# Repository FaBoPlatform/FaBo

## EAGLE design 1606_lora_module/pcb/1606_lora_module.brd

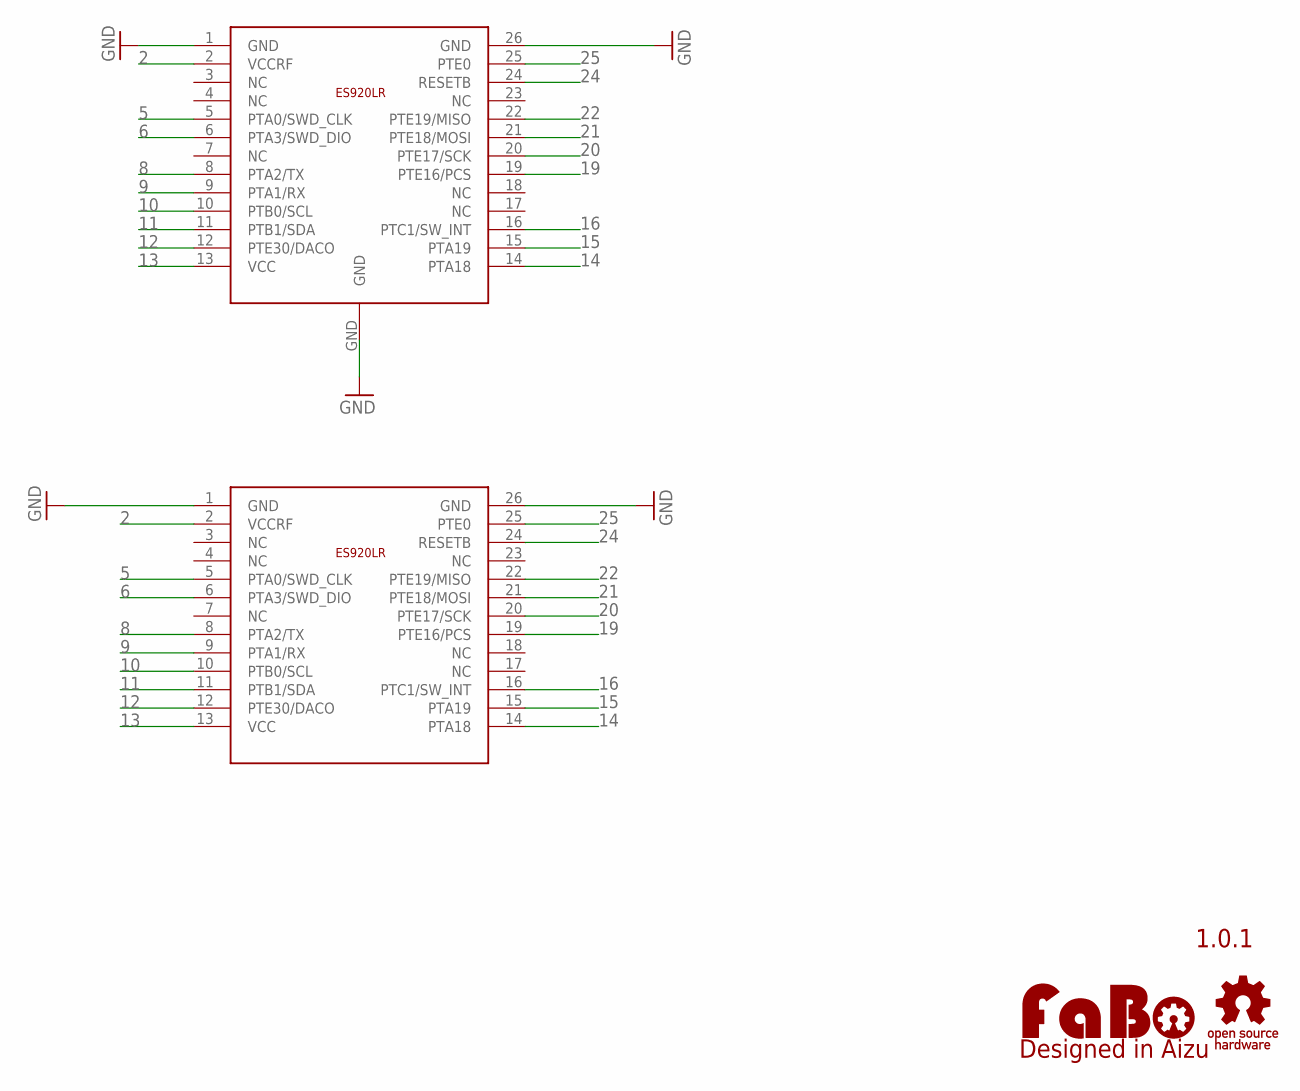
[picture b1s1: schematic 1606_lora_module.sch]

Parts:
U$2: ES920LR
U$3: ES920LR_MODULE; MODULE
U$4: LOGO_OSHW-M_BOTTOM; LOGO_OSHW_M_BOTTOM
U$5: LOGO_FABO-M_BOTTOM; LOGO_FABO_MS_BOTTOM

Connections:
2: U$2.2 (VCCRF), U$3.2 (VCCRF)
5: U$2.5 (PTA0/SWD_CLK), U$3.5 (PTA0/SWD_CLK)
6: U$2.6 (PTA3/SWD_DIO), U$3.6 (PTA3/SWD_DIO)
8: U$2.8 (PTA2/TX), U$3.8 (PTA2/TX)
9: U$2.9 (PTA1/RX), U$3.9 (PTA1/RX)
10: U$2.10 (PTB0/SCL), U$3.10 (PTB0/SCL)
11: U$2.11 (PTB1/SDA), U$3.11 (PTB1/SDA)
12: U$2.12 (PTE30/DACO), U$3.12 (PTE30/DACO)
13: U$2.13 (VCC), U$3.13 (VCC)
14: U$2.14 (PTA18), U$3.14 (PTA18)
15: U$2.15 (PTA19), U$3.15 (PTA19)
16: U$2.16 (PTC1/SW_INT), U$3.16 (PTC1/SW_INT)
19: U$2.19 (PTE16/PCS), U$3.19 (PTE16/PCS)
20: U$2.20 (PTE17/SCK), U$3.20 (PTE17/SCK)
21: U$2.21 (PTE18/MOSI), U$3.21 (PTE18/MOSI)
22: U$2.22 (PTE19/MISO), U$3.22 (PTE19/MISO)
24: U$2.24 (RESETB), U$3.24 (RESETB)
25: U$2.25 (PTE0), U$3.25 (PTE0)
GND: U$2.1 (GND), U$2.26 (GND), U$2.GND, U$3.1 (GND), U$3.26 (GND)

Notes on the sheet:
1.0.1

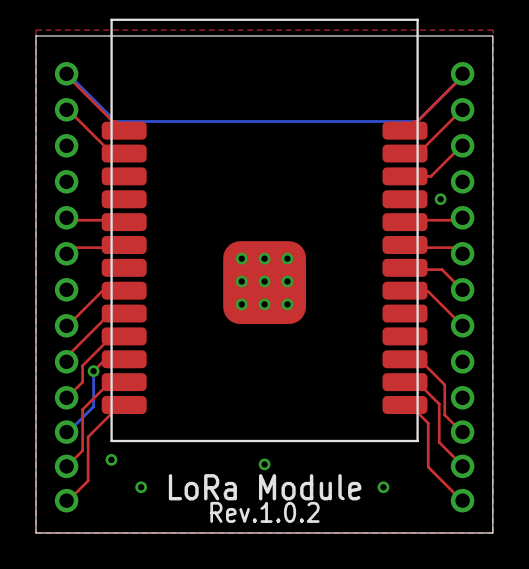
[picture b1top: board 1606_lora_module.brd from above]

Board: 2 copper layers, 25.4 x 27.6 mm, 4 parts (0 on the bottom side), 19 nets.

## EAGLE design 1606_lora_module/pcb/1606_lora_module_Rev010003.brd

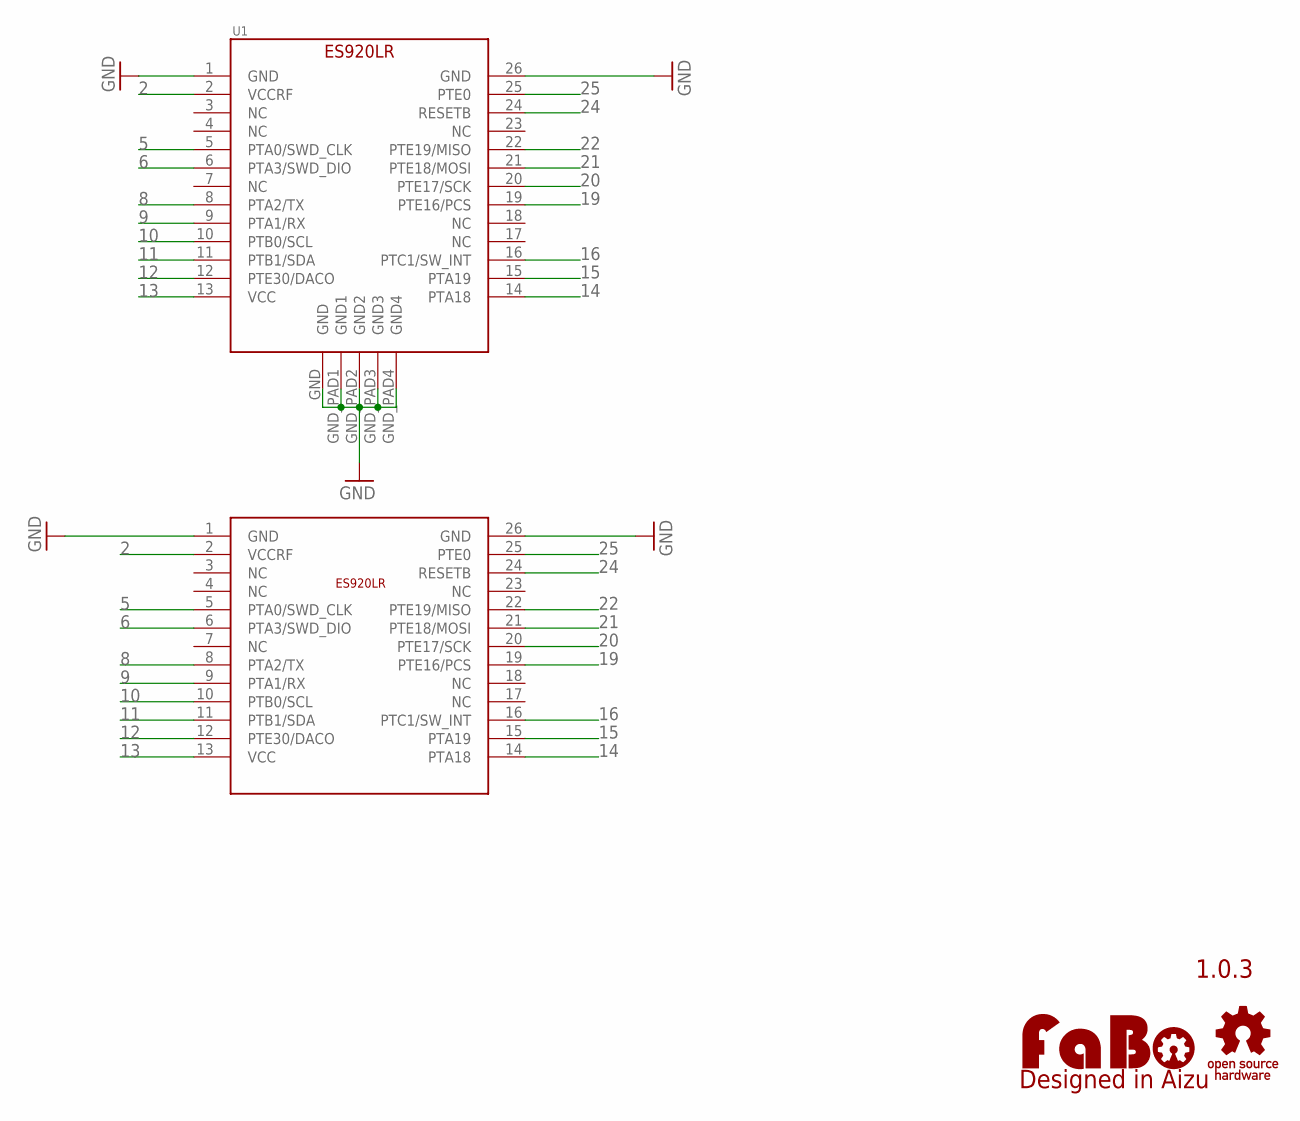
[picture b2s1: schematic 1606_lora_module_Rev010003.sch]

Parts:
U1: ES920LR
U$3: ES920LR_MODULE; MODULE
U$4: LOGO_OSHW-M_BOTTOM; LOGO_OSHW_M_BOTTOM
U$5: LOGO_FABO-M_BOTTOM; LOGO_FABO_MS_BOTTOM

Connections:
2: U1.2 (VCCRF), U$3.2 (VCCRF)
5: U1.5 (PTA0/SWD_CLK), U$3.5 (PTA0/SWD_CLK)
6: U1.6 (PTA3/SWD_DIO), U$3.6 (PTA3/SWD_DIO)
8: U1.8 (PTA2/TX), U$3.8 (PTA2/TX)
9: U1.9 (PTA1/RX), U$3.9 (PTA1/RX)
10: U1.10 (PTB0/SCL), U$3.10 (PTB0/SCL)
11: U1.11 (PTB1/SDA), U$3.11 (PTB1/SDA)
12: U1.12 (PTE30/DACO), U$3.12 (PTE30/DACO)
13: U1.13 (VCC), U$3.13 (VCC)
14: U1.14 (PTA18), U$3.14 (PTA18)
15: U1.15 (PTA19), U$3.15 (PTA19)
16: U1.16 (PTC1/SW_INT), U$3.16 (PTC1/SW_INT)
19: U1.19 (PTE16/PCS), U$3.19 (PTE16/PCS)
20: U1.20 (PTE17/SCK), U$3.20 (PTE17/SCK)
21: U1.21 (PTE18/MOSI), U$3.21 (PTE18/MOSI)
22: U1.22 (PTE19/MISO), U$3.22 (PTE19/MISO)
24: U1.24 (RESETB), U$3.24 (RESETB)
25: U1.25 (PTE0), U$3.25 (PTE0)
GND: U1.1 (GND), U1.26 (GND), U1.GND, U1.GND_PAD1 (GND1), U1.GND_PAD2 (GND2), U1.GND_PAD3 (GND3), U1.GND_PAD4 (GND4), U$3.1 (GND), U$3.26 (GND)

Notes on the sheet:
1.0.3

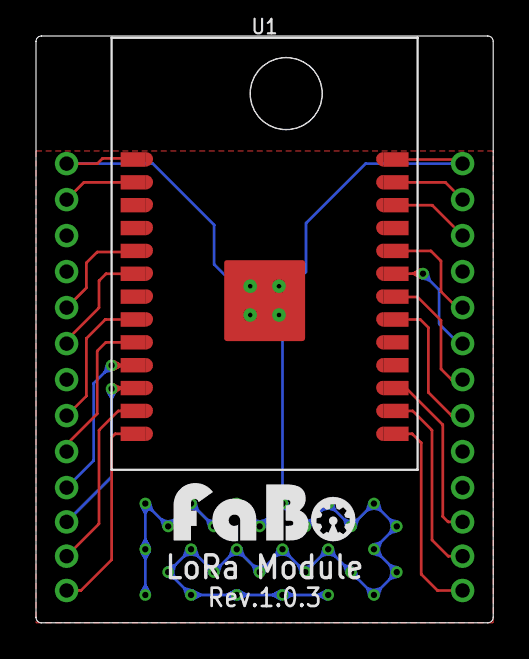
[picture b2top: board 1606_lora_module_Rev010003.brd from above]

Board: 2 copper layers, 25.4 x 32.6 mm, 4 parts (1 on the bottom side), 19 nets.

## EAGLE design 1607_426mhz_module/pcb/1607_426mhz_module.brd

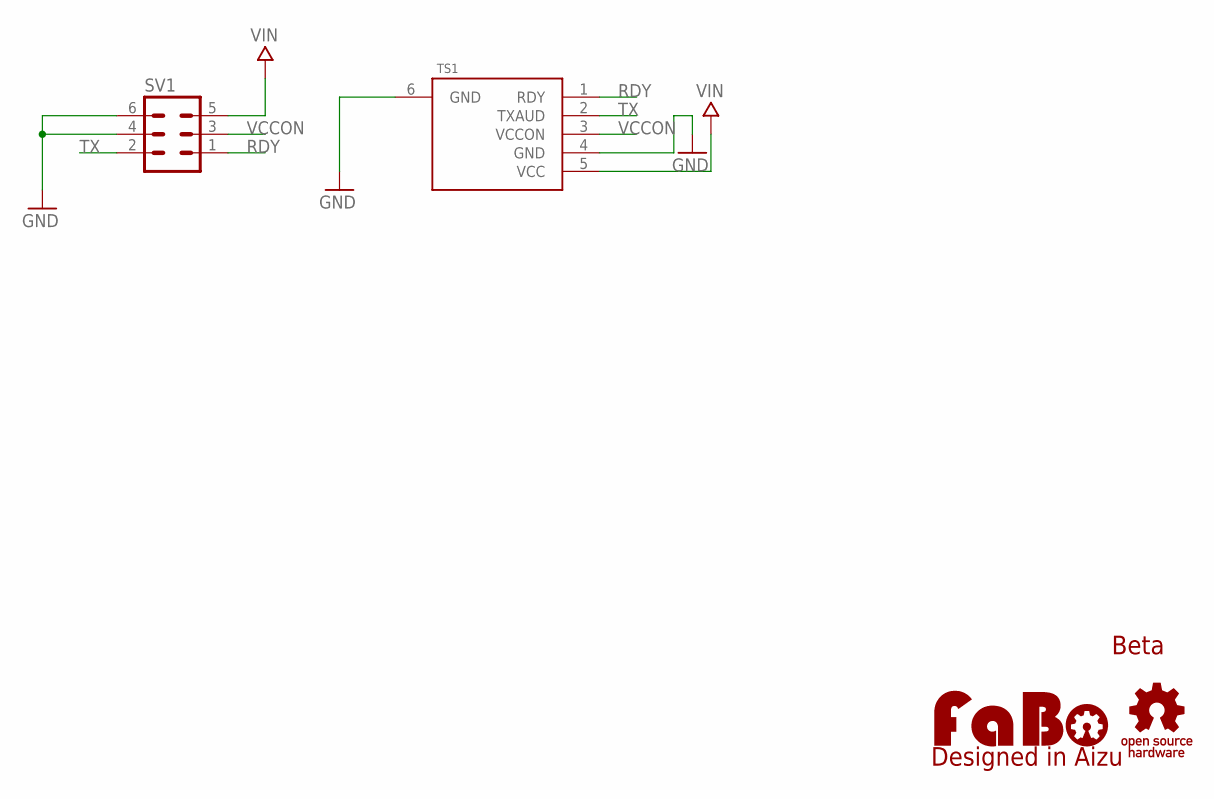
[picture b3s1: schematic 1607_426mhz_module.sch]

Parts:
SV1: MA03-2
TS1: TS01E
U$3: LOGO_OSHW-M_BOTTOM; LOGO_OSHW_M_BOTTOM
U$4: LOGO_FABO-M_BOTTOM; LOGO_FABO_MS_BOTTOM

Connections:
GND: SV1.4, SV1.6, TS1.4 (GND), TS1.6 (GND)
RDY: SV1.1, TS1.1 (RDY)
TX: SV1.2, TS1.2 (TXAUD)
VCCON: SV1.3, TS1.3 (VCCON)
VIN: SV1.5, TS1.5 (VCC)

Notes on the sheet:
Beta

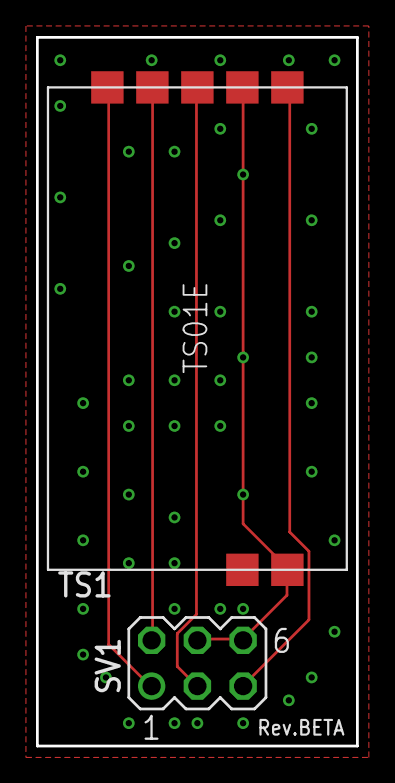
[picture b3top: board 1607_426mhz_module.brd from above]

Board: 2 copper layers, 17.8 x 39.4 mm, 4 parts (0 on the bottom side), 5 nets.

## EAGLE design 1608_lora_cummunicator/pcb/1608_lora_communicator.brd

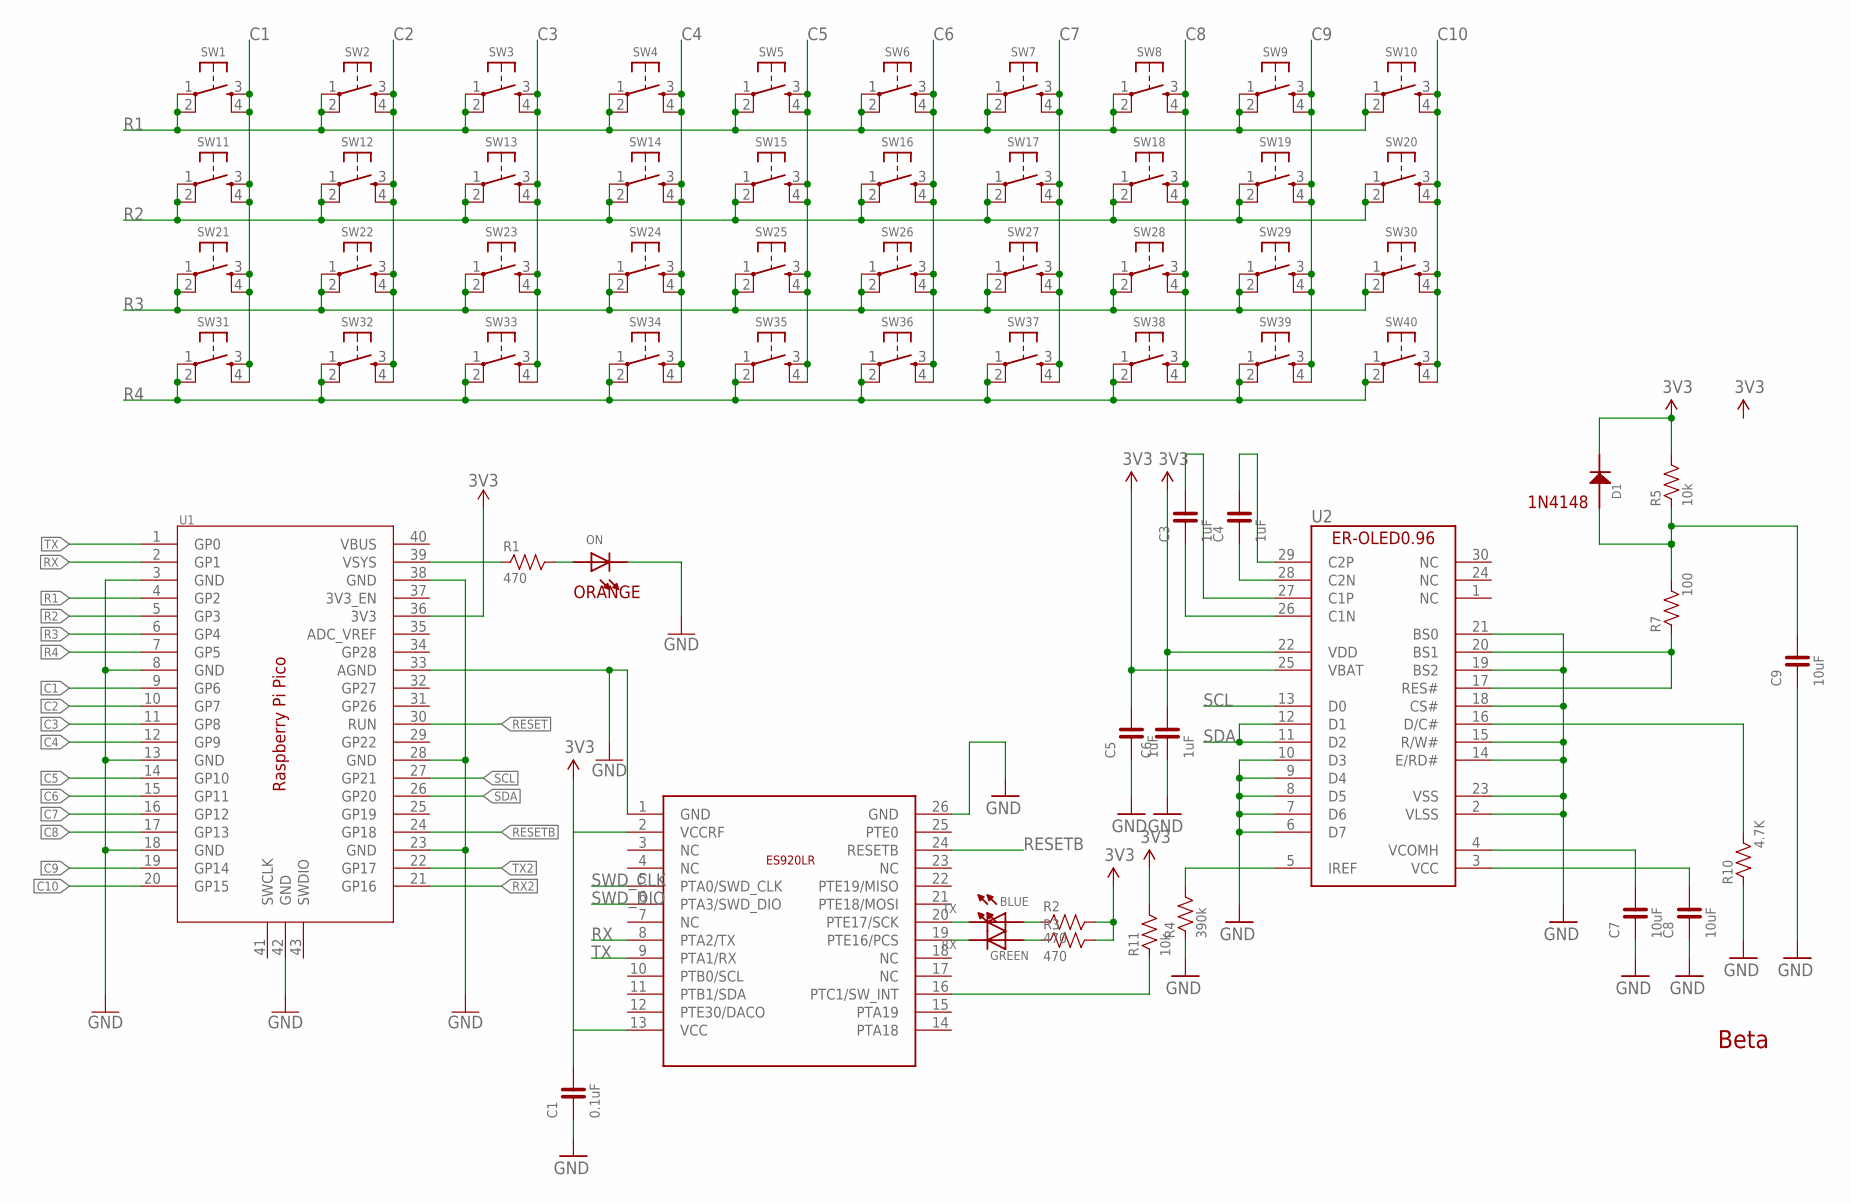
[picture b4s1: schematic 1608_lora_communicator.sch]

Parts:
C1: 0.1uF; 0603-NARROW
C3, C4, C5, C6: 1uF; 0603
C7, C8, C9: 10uF; 0603
D1: 1N4148; 1N4148W
ON: LED-0603; 0603
R1, R2, R3: 470; 0603
R4: 390k; 0603
R5: 10k; 0603
R7: 100; 0603
R10: 4.7K; 0603
R11: 10k; 0603-NARROW
RX: GREEN; 0603
SW1, SW2, SW3, SW4, SW5, SW6, SW7, SW8, SW9, SW10, SW11, SW12, SW13, SW14, SW15, SW16, SW17, SW18, SW19, SW20, SW21, SW22, SW23, SW24, SW25, SW26, SW27, SW28, SW29, SW30, SW31, SW32, SW33, SW34, SW35, SW36, SW37, SW38, SW39, SW40: TACT-SWITCH-6MM; DTS_6_V
TX: BLUE; 0603
U1: RASPBERRY_PI_PICORASPBERRY_PI_PICO_2BY20TH; RASPBERRY_PI_PICO_HEADER_BOTH
U2: ER-OLED0.96-1ER-CON30HT-1; ER-CON30HT-1
U3: ES920LR_MODULE; MODULE

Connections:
3V3: C1.2, C5.2, C6.2, D1.CATHODE, R2.2, R3.2, R5.2, R11.2, U1.36 (3V3), U2.22 (VDD), U2.25 (VBAT), U3.2 (VCCRF), U3.13 (VCC)
C1: SW1.3, SW1.4, SW11.3, SW11.4, SW21.3, SW21.4, SW31.3, SW31.4, U1.9 (GP6)
C2: SW2.3, SW2.4, SW12.3, SW12.4, SW22.3, SW22.4, SW32.3, SW32.4, U1.10 (GP7)
C3: SW3.3, SW3.4, SW13.3, SW13.4, SW23.3, SW23.4, SW33.3, SW33.4, U1.11 (GP8)
C4: SW4.3, SW4.4, SW14.3, SW14.4, SW24.3, SW24.4, SW34.3, SW34.4, U1.12 (GP9)
C5: SW5.3, SW5.4, SW15.3, SW15.4, SW25.3, SW25.4, SW35.3, SW35.4, U1.14 (GP10)
C6: SW6.3, SW6.4, SW16.3, SW16.4, SW26.3, SW26.4, SW36.3, SW36.4, U1.15 (GP11)
C7: SW7.3, SW7.4, SW17.3, SW17.4, SW27.3, SW27.4, SW37.3, SW37.4, U1.16 (GP12)
C8: SW8.3, SW8.4, SW18.3, SW18.4, SW28.3, SW28.4, SW38.3, SW38.4, U1.17 (GP13)
C9: SW9.3, SW9.4, SW19.3, SW19.4, SW29.3, SW29.4, SW39.3, SW39.4, U1.19 (GP14)
C10: SW10.3, SW10.4, SW20.3, SW20.4, SW30.3, SW30.4, SW40.3, SW40.4, U1.20 (GP15)
D/C: R10.2, U2.16 (D/C#)
GND: C1.1, C5.1, C6.1, C7.1, C8.1, C9.1, ON.CATHODE, R4.1, R10.1, U1.3 (GND), U1.8 (GND), U1.13 (GND), U1.18 (GND), U1.23 (GND), U1.28 (GND), U1.33 (AGND), U1.38 (GND), U1.42 (GND), U2.2 (VLSS), U2.6 (D7), U2.7 (D6), U2.8 (D5), U2.9 (D4), U2.10 (D3), U2.14 (E/RD#), U2.15 (R/W#), U2.18 (CS#), U2.19 (BS2), U2.21 (BS0), U2.23 (VSS), U3.1 (GND)
unnamed: R1.1, U1.39 (VSYS)
unnamed: ON.ANODE, R1.2, U3.26 (GND)
unnamed: C3.2, U2.27 (C1P)
unnamed: C3.1, U2.26 (C1N)
unnamed: C4.1, U2.28 (C2N)
unnamed: C4.2, U2.29 (C2P)
unnamed: R4.2, U2.5 (IREF)
unnamed: C7.2, U2.4 (VCOMH)
unnamed: C8.2, U2.3 (VCC)
unnamed: R7.1, U2.17 (RES#), U2.20 (BS1)
unnamed: RX.CATHODE, U3.19 (PTE16/PCS)
unnamed: C9.2, D1.ANODE, R5.1, R7.2
unnamed: TX.CATHODE, U3.20 (PTE17/SCK)
unnamed: R2.1, TX.ANODE
unnamed: R3.1, RX.ANODE
unnamed: R11.1, U3.16 (PTC1/SW_INT)
R1: SW1.1, SW1.2, SW2.1, SW2.2, SW3.1, SW3.2, SW4.1, SW4.2, SW5.1, SW5.2, SW6.1, SW6.2, SW7.1, SW7.2, SW8.1, SW8.2, SW9.1, SW9.2, SW10.1, SW10.2, U1.4 (GP2)
R2: SW11.1, SW11.2, SW12.1, SW12.2, SW13.1, SW13.2, SW14.1, SW14.2, SW15.1, SW15.2, SW16.1, SW16.2, SW17.1, SW17.2, SW18.1, SW18.2, SW19.1, SW19.2, SW20.1, SW20.2, U1.5 (GP3)
R3: SW21.1, SW21.2, SW22.1, SW22.2, SW23.1, SW23.2, SW24.1, SW24.2, SW25.1, SW25.2, SW26.1, SW26.2, SW27.1, SW27.2, SW28.1, SW28.2, SW29.1, SW29.2, SW30.1, SW30.2, U1.6 (GP4)
R4: SW31.1, SW31.2, SW32.1, SW32.2, SW33.1, SW33.2, SW34.1, SW34.2, SW35.1, SW35.2, SW36.1, SW36.2, SW37.1, SW37.2, SW38.1, SW38.2, SW39.1, SW39.2, SW40.1, SW40.2, U1.7 (GP5)
RESET: U1.30 (RUN)
RESETB: U1.24 (GP18), U3.24 (RESETB)
RX: U1.2 (GP1), U3.8 (PTA2/TX)
RX2: U1.21 (GP16)
SCL: U1.27 (GP21), U2.13 (D0)
SDA: U1.26 (GP20), U2.11 (D2), U2.12 (D1)
SWD_CLK: U3.5 (PTA0/SWD_CLK)
SWD_DIO: U3.6 (PTA3/SWD_DIO)
TX: U1.1 (GP0), U3.9 (PTA1/RX)
TX2: U1.22 (GP17)

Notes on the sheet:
Beta
ORANGE
1N4148

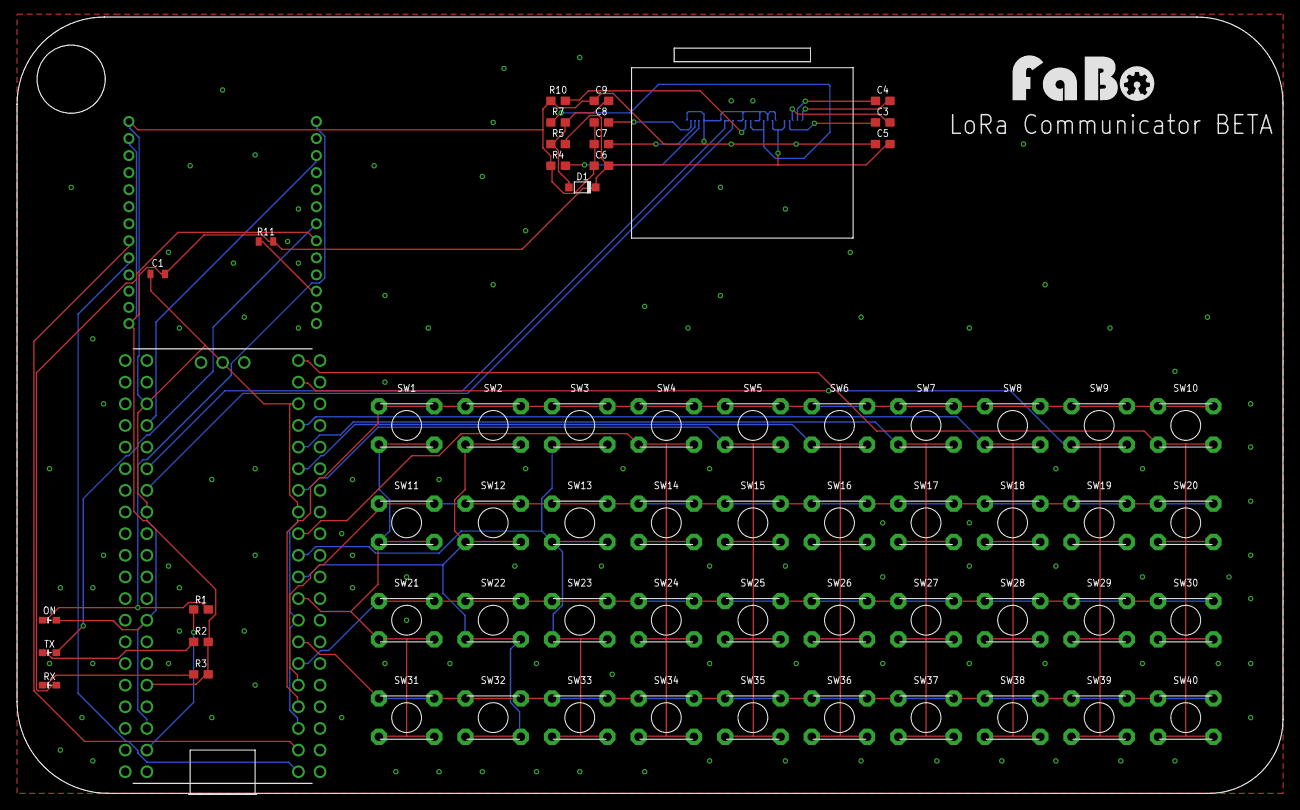
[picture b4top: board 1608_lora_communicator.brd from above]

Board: 2 copper layers, 148.6 x 91.1 mm, 64 parts (0 on the bottom side), 38 nets.

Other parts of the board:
U$2: LOGO_FABO_L

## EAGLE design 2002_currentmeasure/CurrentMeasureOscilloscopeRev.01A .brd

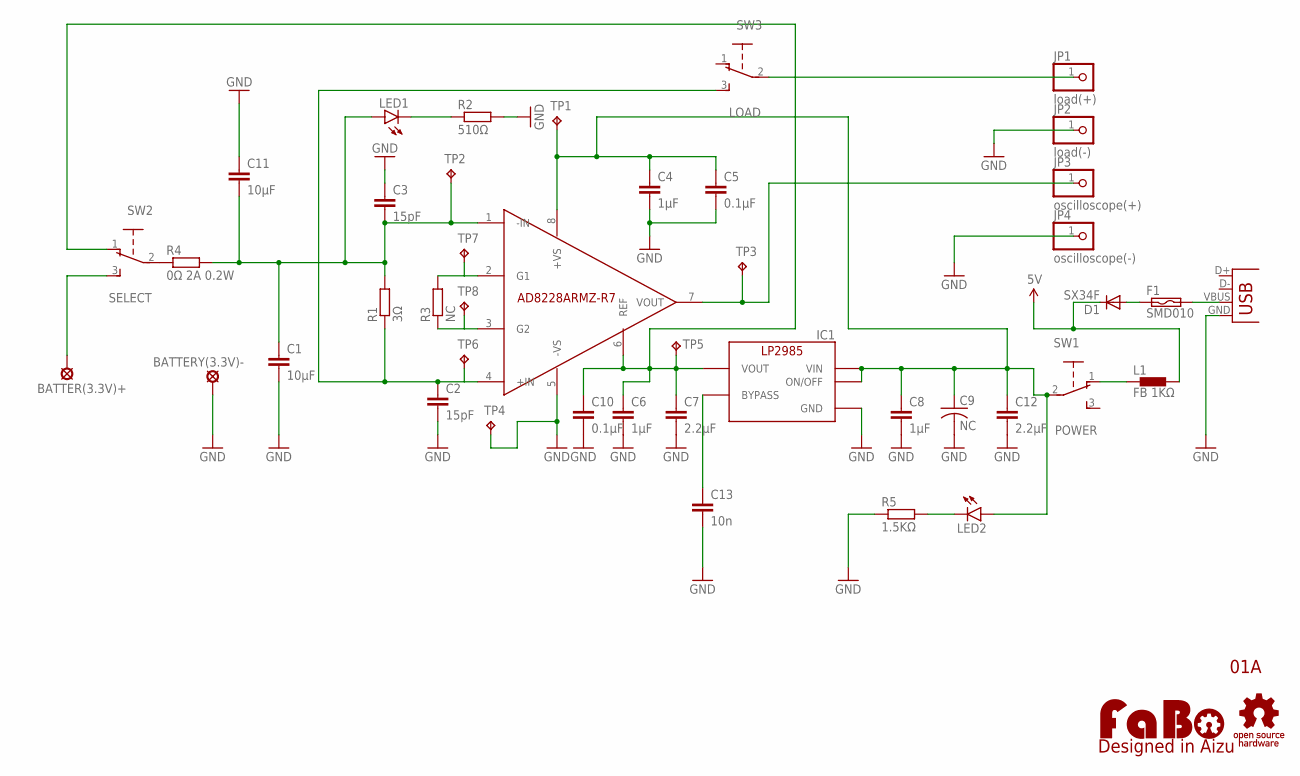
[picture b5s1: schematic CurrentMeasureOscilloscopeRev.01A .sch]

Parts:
BATTER(3.3V)+: SE14
BATTERY(3.3V)-: SE14
C1, C11: 10μF; C0805
C2, C3: 15pF; C0402
C4: 1μF; C0603
C5, C10: 0.1μF; C0402
C6, C8: 1μF; C0805
C7, C12: 2.2μF; C1206K
C9: NC; C2012
C13: 10n; C2012
D1: SX34F; SOD106-R
F1: SMD010
IC1: TI-LP2985-33DBVR; TI-LP2985
JP1: load(+); 1X01
JP2: load(-); 1X01
JP3: oscilloscope(+); 1X01
JP4: oscilloscope(-); 1X01
JP5: USB-B-MICRO_SMD; USB_B_MICRO
L1: FB 1KΩ; 0402
LED1, LED2: LED-EIA0603; EIA0603-LED
R1: 3Ω; M1206
R2: 510Ω; R0402
R3: NC; M1206
R4: 0Ω 2A 0.2W; R0402
R5: 1.5KΩ; R0603
SW1: POWER; EG1218
SW2: SELECT; EG1218
SW3: LOAD; EG1218
TP1, TP2, TP3, TP4, TP5, TP6, TP7, TP8: TPTP13R; TP13R
U1: AD8228ADZY; MSOP08
U$2: LOGO_OSHW-M_BOTTOM; LOGO_OSHW_M_BOTTOM
U$3: LOGO_FABO-M; LOGO_FABO_MS

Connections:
5V: D1.C, L1.2
GND: BATTERY(3.3V)-.MP, C1.2, C2.2, C3.1, C4.2, C5.2, C6.2, C7.2, C8.2, C9.2, C10.2, C11.1, C12.2, C13.2, IC1.2 (GND), JP2.1, JP4.1, JP5.GND, R2.2, R5.1, TP4.TP, U1.5 (-VS)
unnamed: C1.1, C3.2, C11.2, LED1.A, R1.2, R4.2, TP2.TP, U1.1 (-IN)
unnamed: C4.1, C5.1, C8.1, C9.1, C12.1, IC1.1 (VIN), IC1.3 (ON/OFF), LED2.A, SW1.2, TP1.TP, U1.8 (+VS)
unnamed: C2.1, R1.1, SW3.3, TP6.TP, U1.4 (+IN)
unnamed: LED1.C, R2.1
unnamed: JP3.1, TP3.TP, U1.7 (VOUT)
unnamed: R3.2, TP7.TP, U1.2 (G1)
unnamed: R3.1, TP8.TP, U1.3 (G2)
unnamed: BATTER(3.3V)+.MP, SW2.3
unnamed: JP1.1, SW3.2
unnamed: R4.1, SW2.2
unnamed: C6.1, C7.1, C10.1, IC1.5 (VOUT), SW2.1, TP5.TP, U1.6 (REF)
unnamed: C13.1, IC1.4 (BYPASS)
unnamed: LED2.C, R5.2
unnamed: L1.1, SW1.1
unnamed: D1.A, F1.P$1 (1)
unnamed: F1.P$2 (2), JP5.VBUS

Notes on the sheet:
AD8228ARMZ-R7
01A

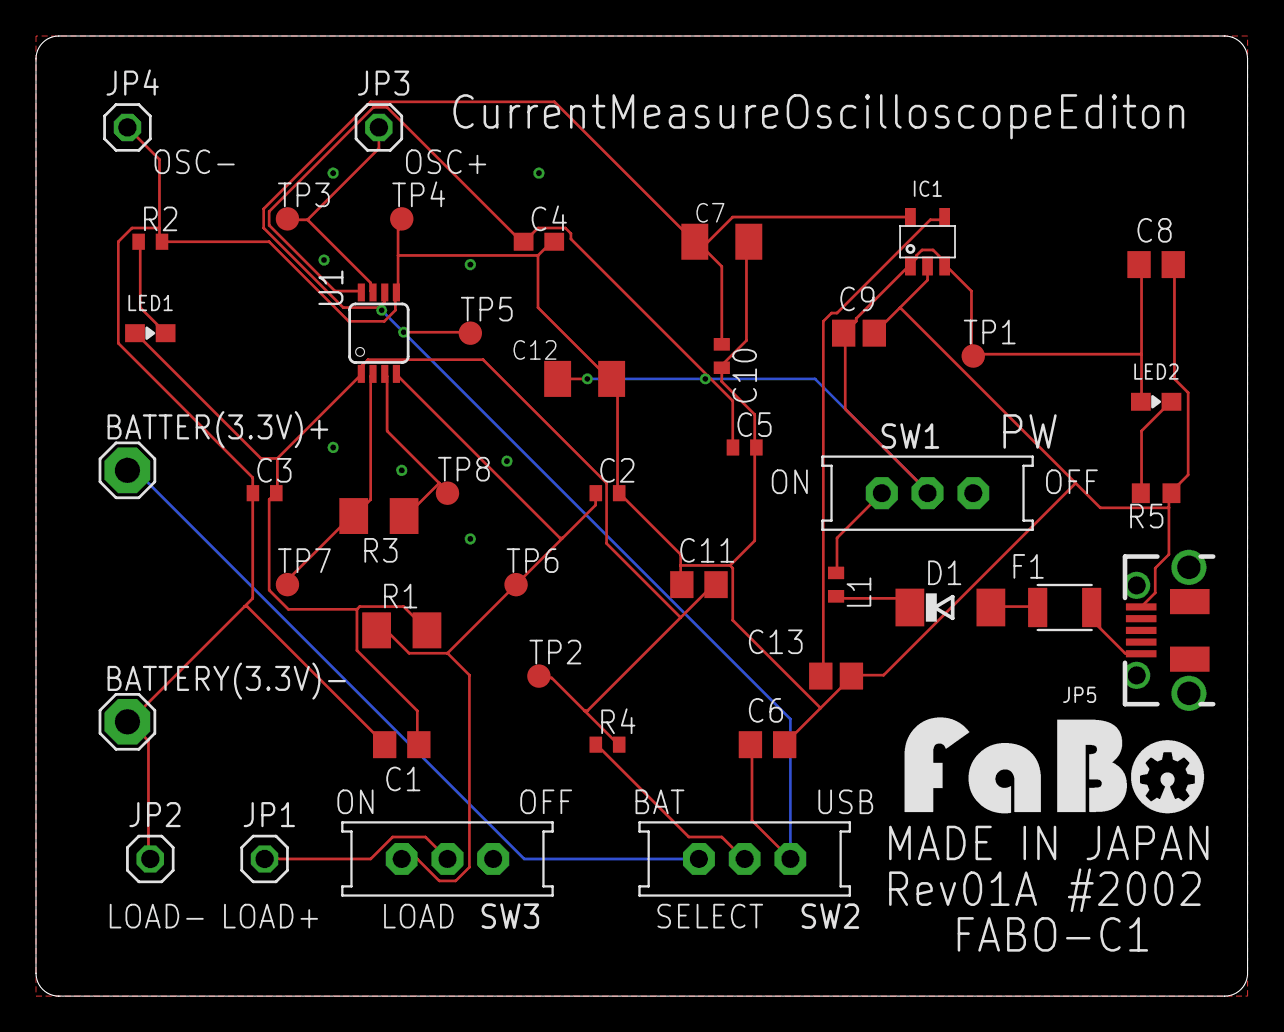
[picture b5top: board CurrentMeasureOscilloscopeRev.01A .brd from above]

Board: 2 copper layers, 67.3 x 53.3 mm, 44 parts (0 on the bottom side), 18 nets.

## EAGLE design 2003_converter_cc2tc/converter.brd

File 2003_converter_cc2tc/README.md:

# #2003 Converter

## Overview

CC DebuggerからTagConnecterへの変換をおこないます。

## 回路図

## Github

https://github.com/FaBoPlatform/FaBo/tree/master/2003_converter_cc2tc

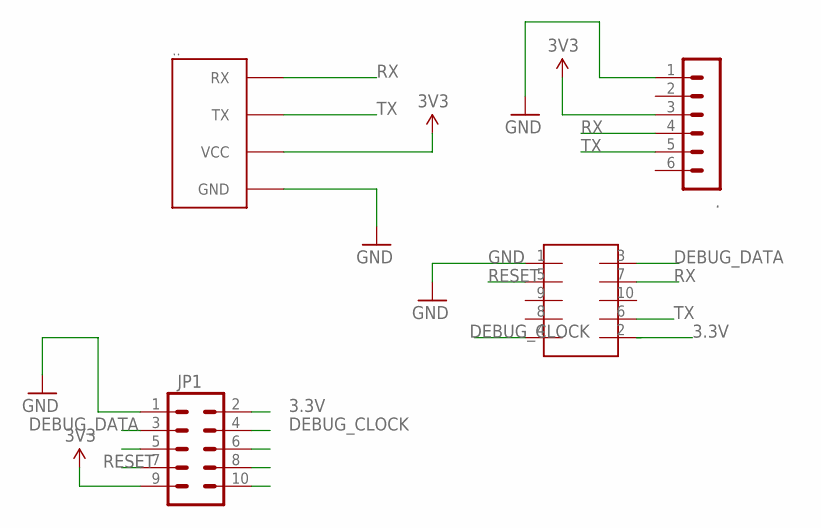
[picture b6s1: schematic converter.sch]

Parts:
.: MA06-1
..: FABO_BRICK_SERIAL-S04B-PASK-2; FABO_BRICK_SERIAL_S04B-PASK-2
JP1: M05X2SHD; 2X5-SHROUDED
U$4: TC-2050-SOCKET

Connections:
3.3V: JP1.2, U$4.2
3V3: ..3, ...VCC, JP1.9
CSN: JP1.5
DEBUG_CLOCK: JP1.4, U$4.4
DEBUG_DATA: JP1.3, U$4.3
GND: ..1, ...GND, JP1.1, U$4.1
MISO: JP1.10
MOSI: JP1.8
RESET: JP1.7, U$4.5
RX: ..4, ...RX, U$4.7
SCLK: JP1.6
TX: ..5, ...TX, U$4.6

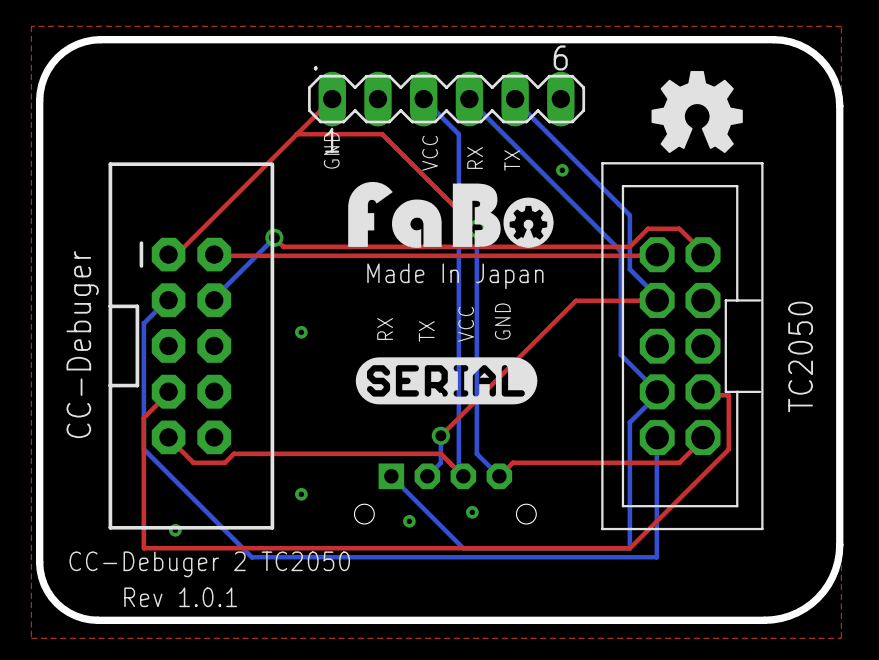
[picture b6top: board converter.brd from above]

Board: 2 copper layers, 44.4 x 32.3 mm, 7 parts (0 on the bottom side), 8 nets.

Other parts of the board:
U$1: LOGO_FABO_M
U$2: LOGO_OSHW_M
U$5: LOGO_SILK_SERIAL2

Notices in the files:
parts and their libraries:
FaBo-Logo: Released under the Creative Commons Attribution-ShareAlike 4.0 License
https://creativecommons.org/licenses/by-sa/4.0
component: Released under the Creative Commons
SparkFun-Connectors: Licensing: CC v3.0 Share-Alike You are welcome to use this library for commercial purposes.
